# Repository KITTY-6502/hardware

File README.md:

# KITTY Computer

the KITTY is a 65c02 homebrew kit microcomputer designed around text mode graphics and cartridge media. It is fully open source, and uses exclusively in-production parts. 

Quick Specs:

* **Bus Speed:** 3Mhz
* **CPU:*** w65c02s @~2.2Mhz (average)
* **RAM:** 28Kb SRAM
* **Video:** Custom, 256x256pixels, a text mode display using a preset font, 32x32 8x8 pixel characters, 16 color palette
* **Sound:** Custom, 8x1 Wavetable Audio, 3 melodic + 1 percussive channels, all with 4bit+4bit stereo volume control.
* **Input:** 40-Key Mechanical Keyboard
* **Media/Expansion:** 2 Cartridge Slots, each with up to 128x32Kb banks.
* **Interrupts:** /IRQ triggered when the video circuit has drawn the last visible pixels on the frame.
* **Output:** RGB PAL (50hz), via a SCART connector.

**[Computer Manual](https://smaldragon.github.io/KITTY)**
**[Schematic](Docs/schematics/v2a.pdf)**

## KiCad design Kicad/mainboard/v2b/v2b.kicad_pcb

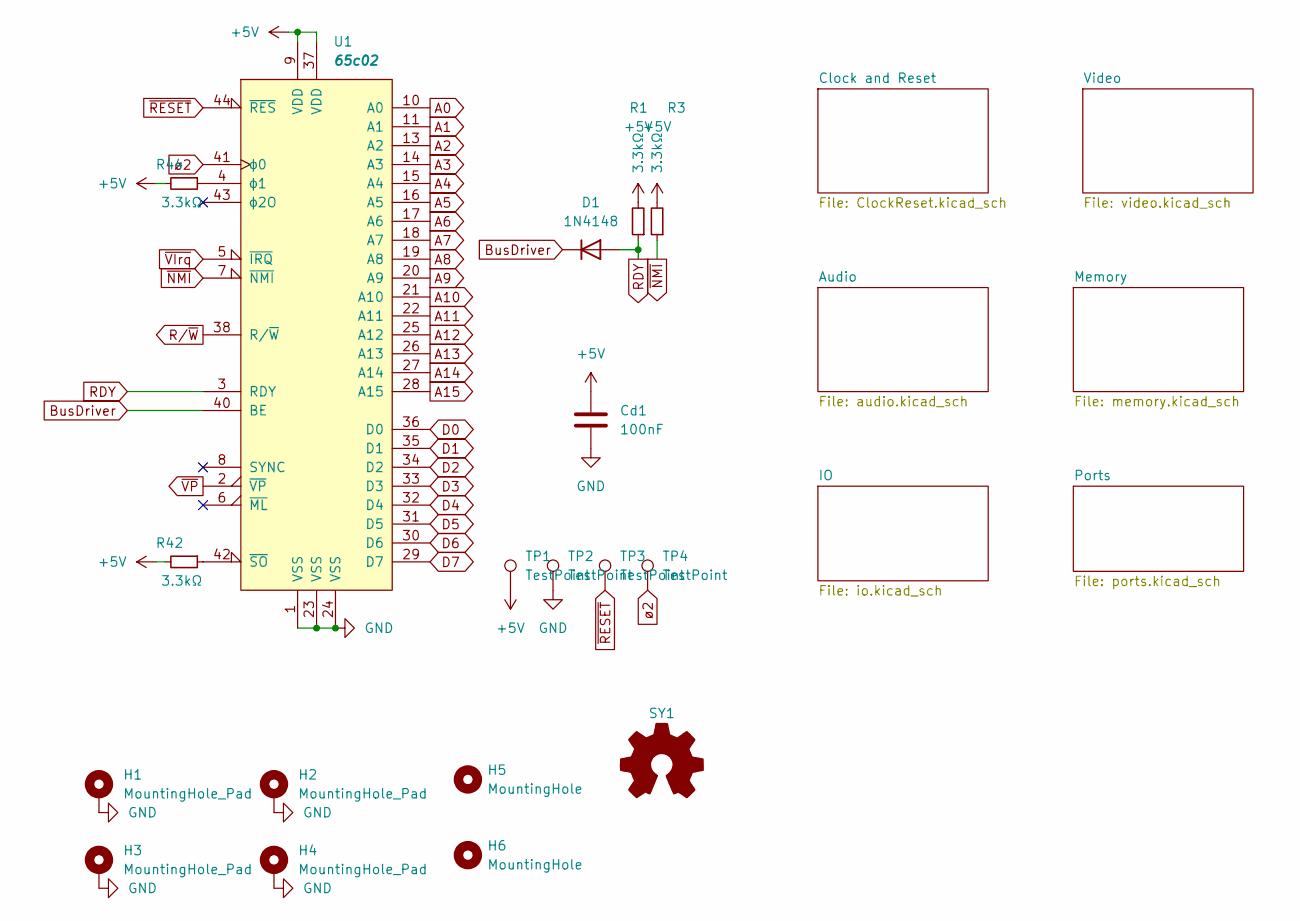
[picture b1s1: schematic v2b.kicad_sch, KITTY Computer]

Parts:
Cd1: 100nF; C_Disc_D3.0mm_W1.6mm_P2.50mm
D1: 1N4148; D_DO-34_SOD68_P7.62mm_Horizontal
H1, H2, H3, H4: MountingHole_Pad; MountingHole_3.2mm_M3_ISO14580_Pad
H5, H6: MountingHole; MountingHole_2.2mm_M2
R1, R3, R42, R44: 3.3kΩ; R_Horizontal
SY1: Logo_Open_Hardware_Small; OSHW-Logo_7.5x8mm_SilkScreen
TP1, TP2, TP3, TP4: TestPoint; TestPoint_Pad_2.0x2.0mm
U1: 65c02; PLCC-44_THT-Socket_TWEAK

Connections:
+5V: Cd1.1, R1.2, R3.2, R42.2, R44.2, TP1.1, U1.9 (VDD), U1.37 (VDD); also elsewhere on the board
A0: U1.10 (A0); also elsewhere on the board
A1: U1.11 (A1); also elsewhere on the board
A2: U1.13 (A2); also elsewhere on the board
A3: U1.14 (A3); also elsewhere on the board
A4: U1.15 (A4); also elsewhere on the board
A5: U1.16 (A5); also elsewhere on the board
A6: U1.17 (A6); also elsewhere on the board
A7: U1.18 (A7); also elsewhere on the board
A8: U1.19 (A8); also elsewhere on the board
A9: U1.20 (A9); also elsewhere on the board
A10: U1.21 (A10); also elsewhere on the board
A11: U1.22 (A11); also elsewhere on the board
A12: U1.25 (A12); also elsewhere on the board
A13: U1.26 (A13); also elsewhere on the board
A14: U1.27 (A14); also elsewhere on the board
A15: U1.28 (A15); also elsewhere on the board
BusDriver: D1.1 (K), U1.40 (BE); also elsewhere on the board
CLK2: TP4.1, U1.41 (ϕ0); also elsewhere on the board
D0: U1.36 (D0); also elsewhere on the board
D1: U1.35 (D1); also elsewhere on the board
D2: U1.34 (D2); also elsewhere on the board
D3: U1.33 (D3); also elsewhere on the board
D4: U1.32 (D4); also elsewhere on the board
D5: U1.31 (D5); also elsewhere on the board
D6: U1.30 (D6); also elsewhere on the board
D7: U1.29 (D7); also elsewhere on the board
GND: Cd1.2, H1.1, H2.1, H3.1, H4.1, TP2.1, U1.1 (VSS), U1.23 (VSS), U1.24 (VSS); also elsewhere on the board
unnamed: R42.1, U1.42 (~SO)
unnamed: R44.1, U1.4 (ϕ1)
RDY: D1.2 (A), R1.1, U1.3 (RDY)
R/~W: U1.38 (R/~W); also elsewhere on the board
~NMI: R3.1, U1.7 (~NMI); also elsewhere on the board
~RESET: TP3.1, U1.44 (~RES); also elsewhere on the board
~VIrq: U1.5 (~IRQ); also elsewhere on the board
~VP: U1.2 (~VP); also elsewhere on the board

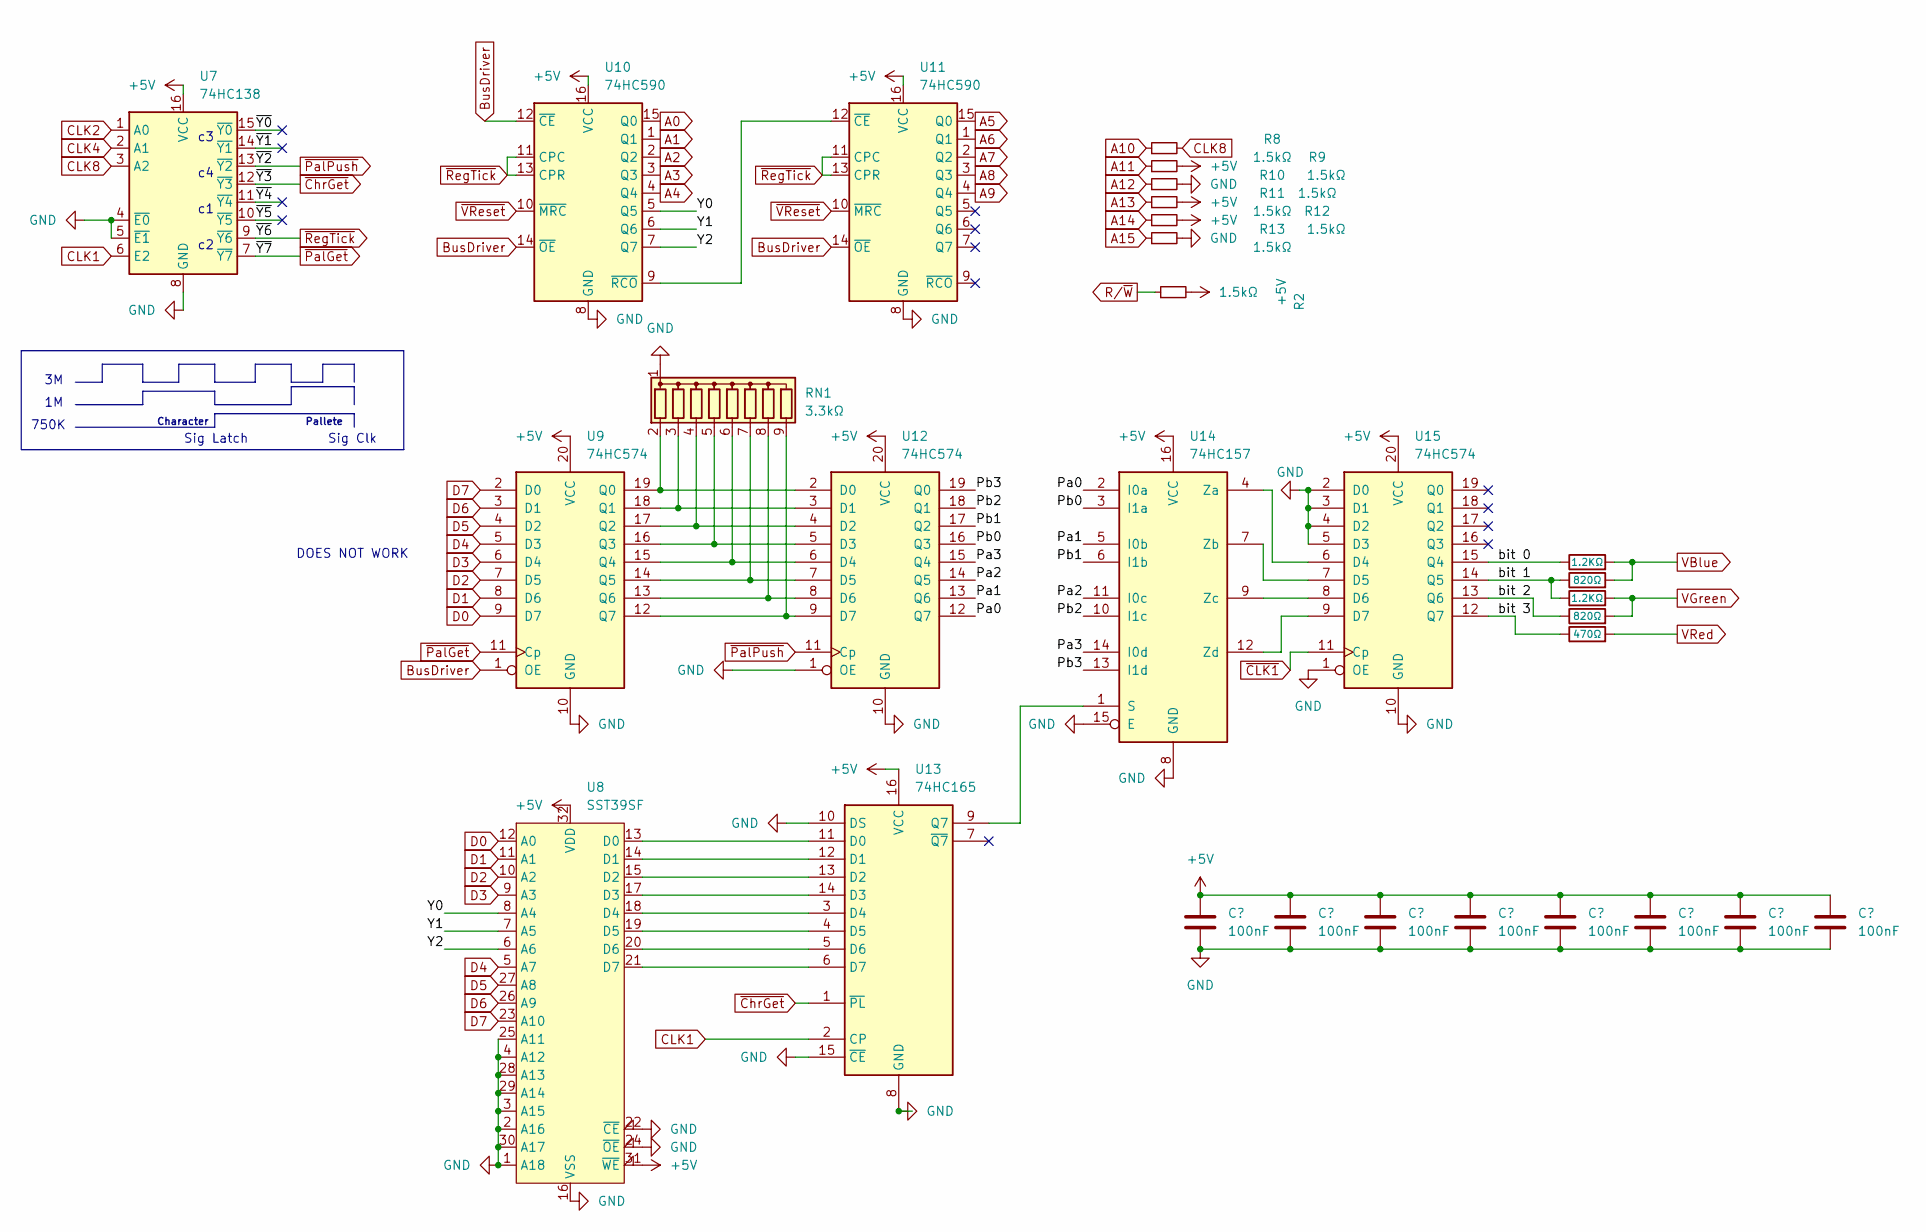
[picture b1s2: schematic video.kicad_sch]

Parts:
Cd8, Cd9, Cd10, Cd11, Cd12, Cd13, Cd14, Cd15: 100nF; C_Disc_D3.0mm_W1.6mm_P2.50mm
R2, R8, R9, R10, R11, R12, R13: 1.5kΩ; R_Horizontal
R14, R16: 1.2KΩ; R_Horizontal
R15, R17: 820Ω; R_Horizontal
R18: 470Ω; R_Horizontal
RN1: 3.3kΩ; R_Array_SIP9
U7: 74HC138; DIP-16_W7.62mm_Socket_LongPads_TWEAK
U8: SST39SF; PLCC-32_THT-Socket_TWEAK
U9, U12, U15: 74HC574; DIP-20_W7.62mm_Socket_LongPads_TWEAK
U10, U11: 74HC590; DIP-16_W7.62mm_Socket_LongPads_TWEAK
U13: 74HC165; DIP-16_W7.62mm_Socket_LongPads_TWEAK
U14: 74HC157; DIP-16_W7.62mm_Socket_LongPads_TWEAK

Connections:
+5V: Cd8.1, Cd9.1, Cd10.1, Cd11.1, Cd12.1, Cd13.1, Cd14.1, Cd15.1, R2.2, R9.2, R11.2, R12.2, U7.16 (VCC), U8.31 (~WE), U8.32 (VDD), U9.20 (VCC), U10.16 (VCC), U11.16 (VCC), U12.20 (VCC), U13.16 (VCC), U14.16 (VCC), U15.20 (VCC); also elsewhere on the board
/Video/Pa0: U12.12 (Q7), U14.2 (I0a)
/Video/Pa1: U12.13 (Q6), U14.5 (I0b)
/Video/Pa2: U12.14 (Q5), U14.11 (I0c)
/Video/Pa3: U12.15 (Q4), U14.14 (I0d)
/Video/Pb0: U12.16 (Q3), U14.3 (I1a)
/Video/Pb1: U12.17 (Q2), U14.6 (I1b)
/Video/Pb2: U12.18 (Q1), U14.10 (I1c)
/Video/Pb3: U12.19 (Q0), U14.13 (I1d)
/Video/Y0: U8.8 (A4), U10.5 (Q5)
/Video/Y1: U8.7 (A5), U10.6 (Q6)
/Video/Y2: U8.6 (A6), U10.7 (Q7)
/Video/bit 0: R14.1, U15.15 (Q4)
/Video/bit 1: R15.1, R16.1, U15.14 (Q5)
/Video/bit 2: R17.1, U15.13 (Q6)
/Video/bit 3: R18.1, U15.12 (Q7)
/Video/~Y0: U7.15 (~Y0)
/Video/~Y1: U7.14 (~Y1)
/Video/~Y4: U7.11 (~Y4)
/Video/~Y5: U7.10 (~Y5)
A0: U10.15 (Q0); also elsewhere on the board
A1: U10.1 (Q1); also elsewhere on the board
A2: U10.2 (Q2); also elsewhere on the board
A3: U10.3 (Q3); also elsewhere on the board
A4: U10.4 (Q4); also elsewhere on the board
A5: U11.15 (Q0); also elsewhere on the board
A6: U11.1 (Q1); also elsewhere on the board
A7: U11.2 (Q2); also elsewhere on the board
A8: U11.3 (Q3); also elsewhere on the board
A9: U11.4 (Q4); also elsewhere on the board
A10: R8.1; also elsewhere on the board
A11: R9.1; also elsewhere on the board
A12: R10.1; also elsewhere on the board
A13: R11.1; also elsewhere on the board
A14: R12.1; also elsewhere on the board
A15: R13.1; also elsewhere on the board
BusDriver: U9.1 (OE), U10.12 (~CE), U10.14 (~OE), U11.14 (~OE); also elsewhere on the board
CLK1: U7.6 (E2), U13.2 (CP); also elsewhere on the board
CLK2: U7.1 (A0); also elsewhere on the board
CLK4: U7.2 (A1); also elsewhere on the board
CLK8: R8.2, U7.3 (A2); also elsewhere on the board
D0: U8.12 (A0), U9.9 (D7); also elsewhere on the board
D1: U8.11 (A1), U9.8 (D6); also elsewhere on the board
D2: U8.10 (A2), U9.7 (D5); also elsewhere on the board
D3: U8.9 (A3), U9.6 (D4); also elsewhere on the board
D4: U8.5 (A7), U9.5 (D3); also elsewhere on the board
D5: U8.27 (A8), U9.4 (D2); also elsewhere on the board
D6: U8.26 (A9), U9.3 (D1); also elsewhere on the board
D7: U8.23 (A10), U9.2 (D0); also elsewhere on the board
GND: Cd8.2, Cd9.2, Cd10.2, Cd11.2, Cd12.2, Cd13.2, Cd14.2, Cd15.2, R10.2, R13.2, RN1.1 (common), U7.4 (~E0), U7.5 (~E1), U7.8 (GND), U8.1 (A18), U8.2 (A16), U8.3 (A15), U8.4 (A12), U8.16 (VSS), U8.22 (~CE), U8.24 (~OE), U8.25 (A11), U8.28 (A13), U8.29 (A14), U8.30 (A17), U9.10 (GND), U10.8 (GND), U11.8 (GND), U12.1 (OE), U12.10 (GND), U13.8 (GND), U13.10 (DS), U13.15 (~CE), U14.8 (GND), U14.15 (E), U15.1 (OE), U15.2 (D0), U15.3 (D1), U15.4 (D2), U15.5 (D3), U15.10 (GND); also elsewhere on the board
unnamed: RN1.2 (R1), U9.19 (Q0), U12.2 (D0)
unnamed: RN1.3 (R2), U9.18 (Q1), U12.3 (D1)
unnamed: RN1.4 (R3), U9.17 (Q2), U12.4 (D2)
unnamed: RN1.5 (R4), U9.16 (Q3), U12.5 (D3)
unnamed: RN1.6 (R5), U9.15 (Q4), U12.6 (D4)
unnamed: RN1.7 (R6), U9.14 (Q5), U12.7 (D5)
unnamed: RN1.8 (R7), U9.13 (Q6), U12.8 (D6)
unnamed: RN1.9 (R8), U9.12 (Q7), U12.9 (D7)
unnamed: U10.9 (~RCO), U11.12 (~CE)
unnamed: U8.13 (D0), U13.11 (D0)
unnamed: U8.14 (D1), U13.12 (D1)
unnamed: U8.15 (D2), U13.13 (D2)
unnamed: U8.17 (D3), U13.14 (D3)
unnamed: U8.18 (D4), U13.3 (D4)
unnamed: U8.19 (D5), U13.4 (D5)
unnamed: U8.20 (D6), U13.5 (D6)
unnamed: U8.21 (D7), U13.6 (D7)
unnamed: U13.9 (Q7), U14.1 (S)
unnamed: U14.4 (Za), U15.6 (D4)
unnamed: U14.7 (Zb), U15.7 (D5)
unnamed: U14.9 (Zc), U15.8 (D6)
unnamed: U14.12 (Zd), U15.9 (D7)
R/~W: R2.1; also elsewhere on the board
VBlue: R14.2, R15.2; also elsewhere on the board
VGreen: R16.2, R17.2; also elsewhere on the board
VRed: R18.2; also elsewhere on the board
~CLK1: U15.11 (Cp); also elsewhere on the board
~ChrGet: U7.12 (~Y3), U13.1 (~PL)
~PalGet: U7.7 (~Y7), U9.11 (Cp)
~PalPush: U7.13 (~Y2), U12.11 (Cp)
~RegTick: U7.9 (~Y6), U10.11 (CPC), U10.13 (CPR), U11.11 (CPC), U11.13 (CPR)
~VReset: U10.10 (~MRC), U11.10 (~MRC); also elsewhere on the board

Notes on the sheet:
Pallete
750K
Sig Clk
Character
DOES NOT WORK
Sig Latch

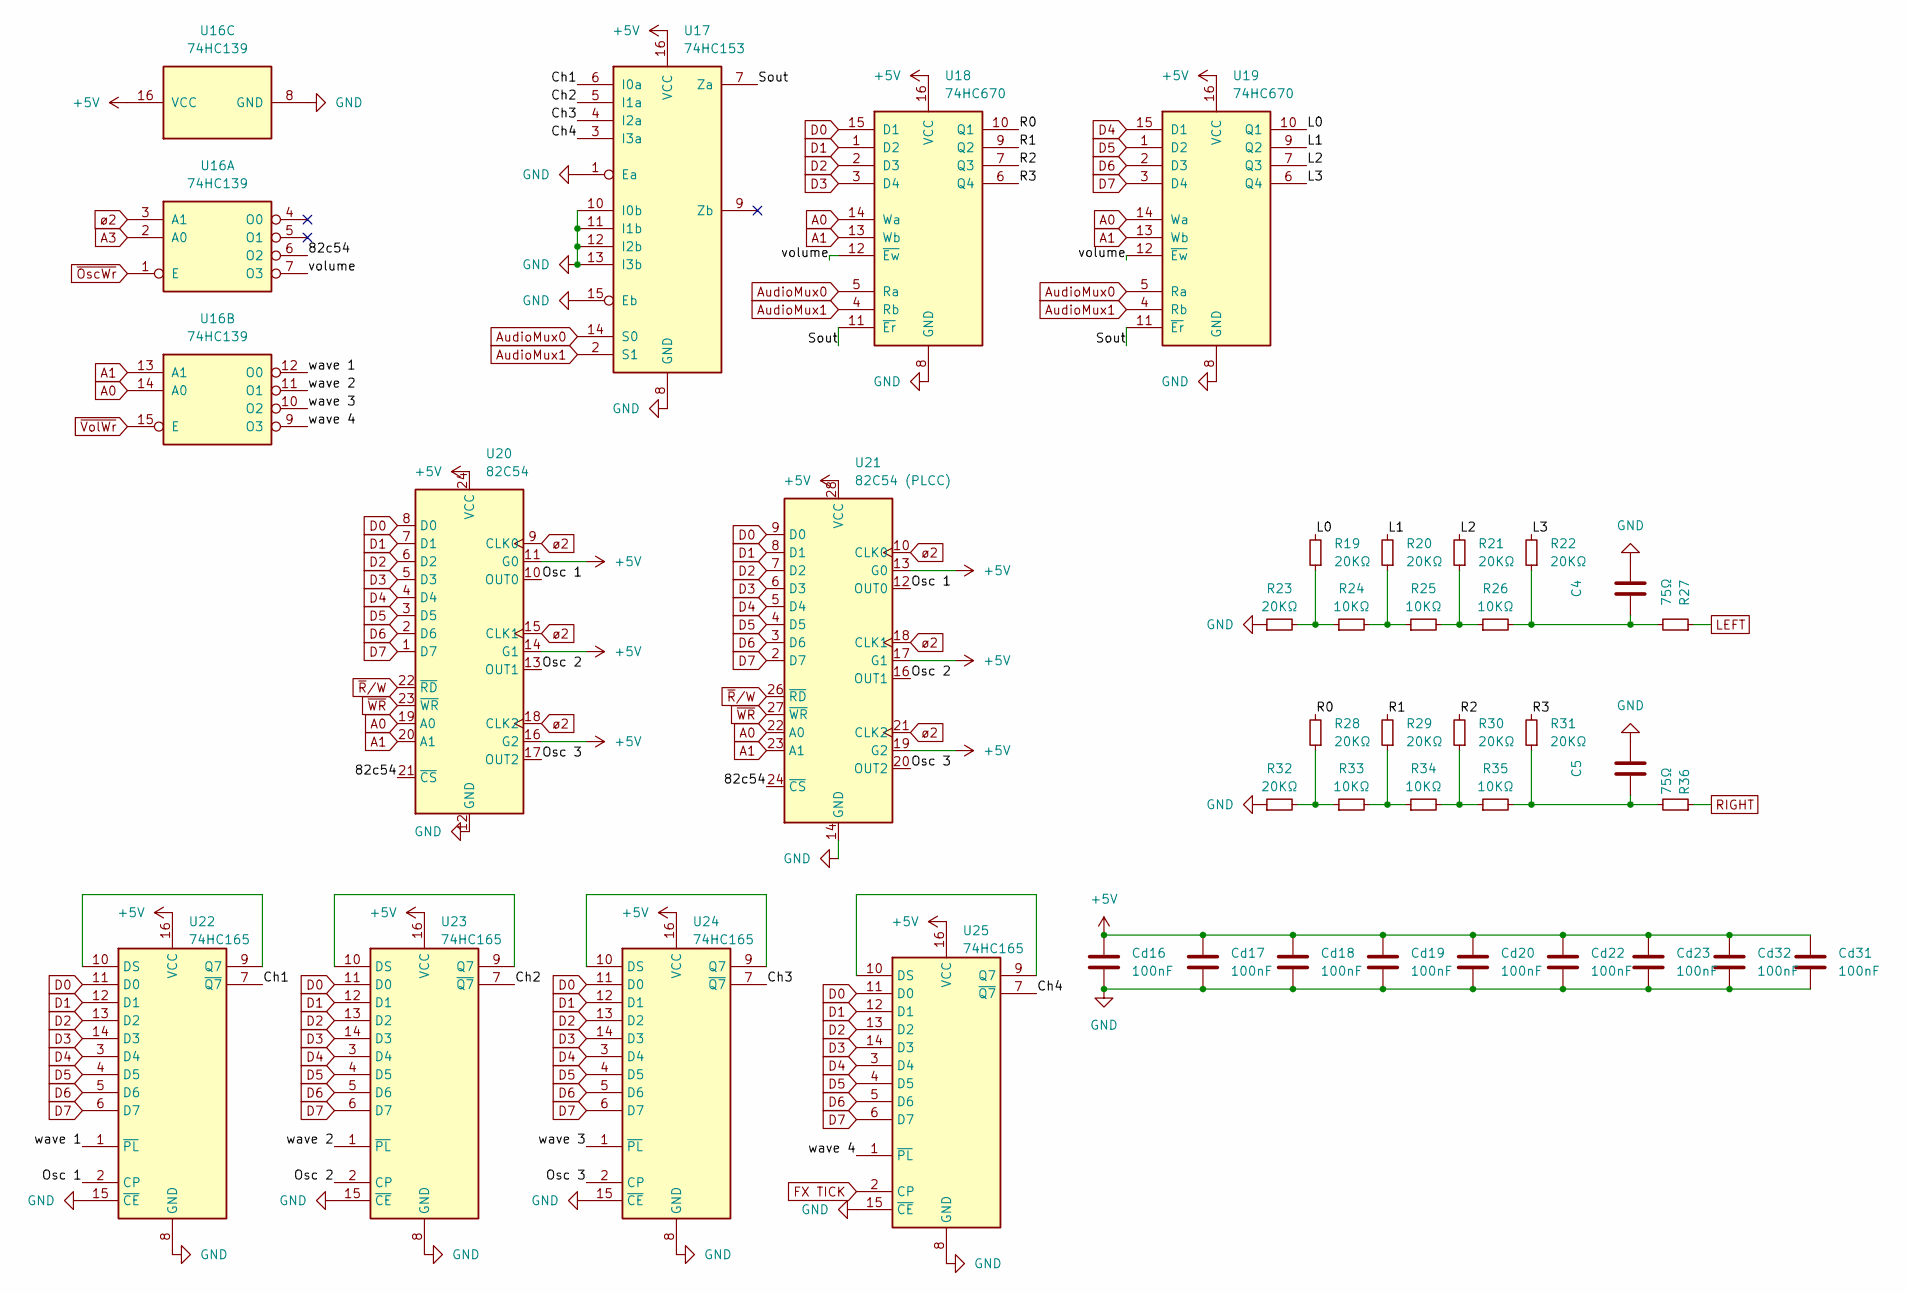
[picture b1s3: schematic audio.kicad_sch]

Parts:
C4, C5: 100nF; C_Disc_D3.0mm_W1.6mm_P2.50mm
Cd16, Cd17, Cd18, Cd19, Cd20, Cd22, Cd23, Cd31, Cd32: 100nF; C_Disc_D3.0mm_W1.6mm_P2.50mm
R19, R20, R21, R22, R23, R28, R29, R30, R31, R32: 20KΩ; RESISTOR VERT_WIDE
R24, R25, R26, R33, R34, R35: 10KΩ; RESISTOR VERT_WIDE
R27, R36: 75Ω; RESISTOR VERT_WIDE
U16: 74HC139; DIP-16_W7.62mm_Socket_LongPads_TWEAK
U17: 74HC153; DIP-16_W7.62mm_Socket_LongPads_TWEAK
U18, U19: 74HC670; DIP-16_W7.62mm_Socket_LongPads_TWEAK
U20: 82C54; DIP-24_W15.24mm_Socket_TWEAK
U21: 82C54 (PLCC); PLCC-28_THT-Socket_TWEAK
U22, U23, U24, U25: 74HC165; DIP-16_W7.62mm_Socket_LongPads_TWEAK

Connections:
+5V: Cd16.1, Cd17.1, Cd18.1, Cd19.1, Cd20.1, Cd22.1, Cd23.1, Cd31.1, Cd32.1, U16.16 (VCC), U17.16 (VCC), U18.16 (VCC), U19.16 (VCC), U20.11 (G0), U20.14 (G1), U20.16 (G2), U20.24 (VCC), U21.13 (G0), U21.17 (G1), U21.19 (G2), U21.28 (VCC), U22.16 (VCC), U23.16 (VCC), U24.16 (VCC), U25.16 (VCC); also elsewhere on the board
/Audio/82c54: U16.6 (O2), U20.21 (~CS), U21.24 (~CS)
/Audio/Ch1: U17.6 (I0a), U22.7 (~Q7)
/Audio/Ch2: U17.5 (I1a), U23.7 (~Q7)
/Audio/Ch3: U17.4 (I2a), U24.7 (~Q7)
/Audio/Ch4: U17.3 (I3a), U25.7 (~Q7)
/Audio/L0: R19.2, U19.10 (Q1)
/Audio/L1: R20.2, U19.9 (Q2)
/Audio/L2: R21.2, U19.7 (Q3)
/Audio/L3: R22.2, U19.6 (Q4)
/Audio/Osc 1: U20.10 (OUT0), U21.12 (OUT0), U22.2 (CP)
/Audio/Osc 2: U20.13 (OUT1), U21.16 (OUT1), U23.2 (CP)
/Audio/Osc 3: U20.17 (OUT2), U21.20 (OUT2), U24.2 (CP)
/Audio/R0: R28.2, U18.10 (Q1)
/Audio/R1: R29.2, U18.9 (Q2)
/Audio/R2: R30.2, U18.7 (Q3)
/Audio/R3: R31.2, U18.6 (Q4)
/Audio/Sout: U17.7 (Za), U18.11 (~Er), U19.11 (~Er)
/Audio/volume: U16.7 (O3), U18.12 (~Ew), U19.12 (~Ew)
/Audio/wave 1: U16.12 (O0), U22.1 (~PL)
/Audio/wave 2: U16.11 (O1), U23.1 (~PL)
/Audio/wave 3: U16.10 (O2), U24.1 (~PL)
/Audio/wave 4: U16.9 (O3), U25.1 (~PL)
A0: U16.14 (A0), U18.14 (Wa), U19.14 (Wa), U20.19 (A0), U21.22 (A0); also elsewhere on the board
A1: U16.13 (A1), U18.13 (Wb), U19.13 (Wb), U20.20 (A1), U21.23 (A1); also elsewhere on the board
A3: U16.2 (A0); also elsewhere on the board
AudioMux0: U17.14 (S0), U18.5 (Ra), U19.5 (Ra); also elsewhere on the board
AudioMux1: U17.2 (S1), U18.4 (Rb), U19.4 (Rb); also elsewhere on the board
CLK2: U16.3 (A1), U20.9 (CLK0), U20.15 (CLK1), U20.18 (CLK2), U21.10 (CLK0), U21.18 (CLK1), U21.21 (CLK2); also elsewhere on the board
D0: U18.15 (D1), U20.8 (D0), U21.9 (D0), U22.11 (D0), U23.11 (D0), U24.11 (D0), U25.11 (D0); also elsewhere on the board
D1: U18.1 (D2), U20.7 (D1), U21.8 (D1), U22.12 (D1), U23.12 (D1), U24.12 (D1), U25.12 (D1); also elsewhere on the board
D2: U18.2 (D3), U20.6 (D2), U21.7 (D2), U22.13 (D2), U23.13 (D2), U24.13 (D2), U25.13 (D2); also elsewhere on the board
D3: U18.3 (D4), U20.5 (D3), U21.6 (D3), U22.14 (D3), U23.14 (D3), U24.14 (D3), U25.14 (D3); also elsewhere on the board
D4: U19.15 (D1), U20.4 (D4), U21.5 (D4), U22.3 (D4), U23.3 (D4), U24.3 (D4), U25.3 (D4); also elsewhere on the board
D5: U19.1 (D2), U20.3 (D5), U21.4 (D5), U22.4 (D5), U23.4 (D5), U24.4 (D5), U25.4 (D5); also elsewhere on the board
D6: U19.2 (D3), U20.2 (D6), U21.3 (D6), U22.5 (D6), U23.5 (D6), U24.5 (D6), U25.5 (D6); also elsewhere on the board
D7: U19.3 (D4), U20.1 (D7), U21.2 (D7), U22.6 (D7), U23.6 (D7), U24.6 (D7), U25.6 (D7); also elsewhere on the board
FX TICK: U25.2 (CP); also elsewhere on the board
GND: C4.1, C5.1, Cd16.2, Cd17.2, Cd18.2, Cd19.2, Cd20.2, Cd22.2, Cd23.2, Cd31.2, Cd32.2, R23.1, R32.1, U16.8 (GND), U17.1 (Ea), U17.8 (GND), U17.10 (I0b), U17.11 (I1b), U17.12 (I2b), U17.13 (I3b), U17.15 (Eb), U18.8 (GND), U19.8 (GND), U20.12 (GND), U21.14 (GND), U22.8 (GND), U22.15 (~CE), U23.8 (GND), U23.15 (~CE), U24.8 (GND), U24.15 (~CE), U25.8 (GND), U25.15 (~CE); also elsewhere on the board
LEFT: R27.1; also elsewhere on the board
unnamed: C4.2, R22.1, R26.2, R27.2
unnamed: C5.2, R31.1, R35.2, R36.2
unnamed: R19.1, R23.2, R24.1
unnamed: R20.1, R24.2, R25.1
unnamed: R21.1, R25.2, R26.1
unnamed: R28.1, R32.2, R33.1
unnamed: R29.1, R33.2, R34.1
unnamed: R30.1, R34.2, R35.1
unnamed: U22.9 (Q7), U22.10 (DS)
unnamed: U23.9 (Q7), U23.10 (DS)
unnamed: U24.9 (Q7), U24.10 (DS)
unnamed: U25.9 (Q7), U25.10 (DS)
RIGHT: R36.1; also elsewhere on the board
~OscWr: U16.1 (E); also elsewhere on the board
~R/W: U20.22 (~RD), U21.26 (~RD); also elsewhere on the board
~VolWr: U16.15 (E); also elsewhere on the board
~WR: U20.23 (~WR), U21.27 (~WR); also elsewhere on the board

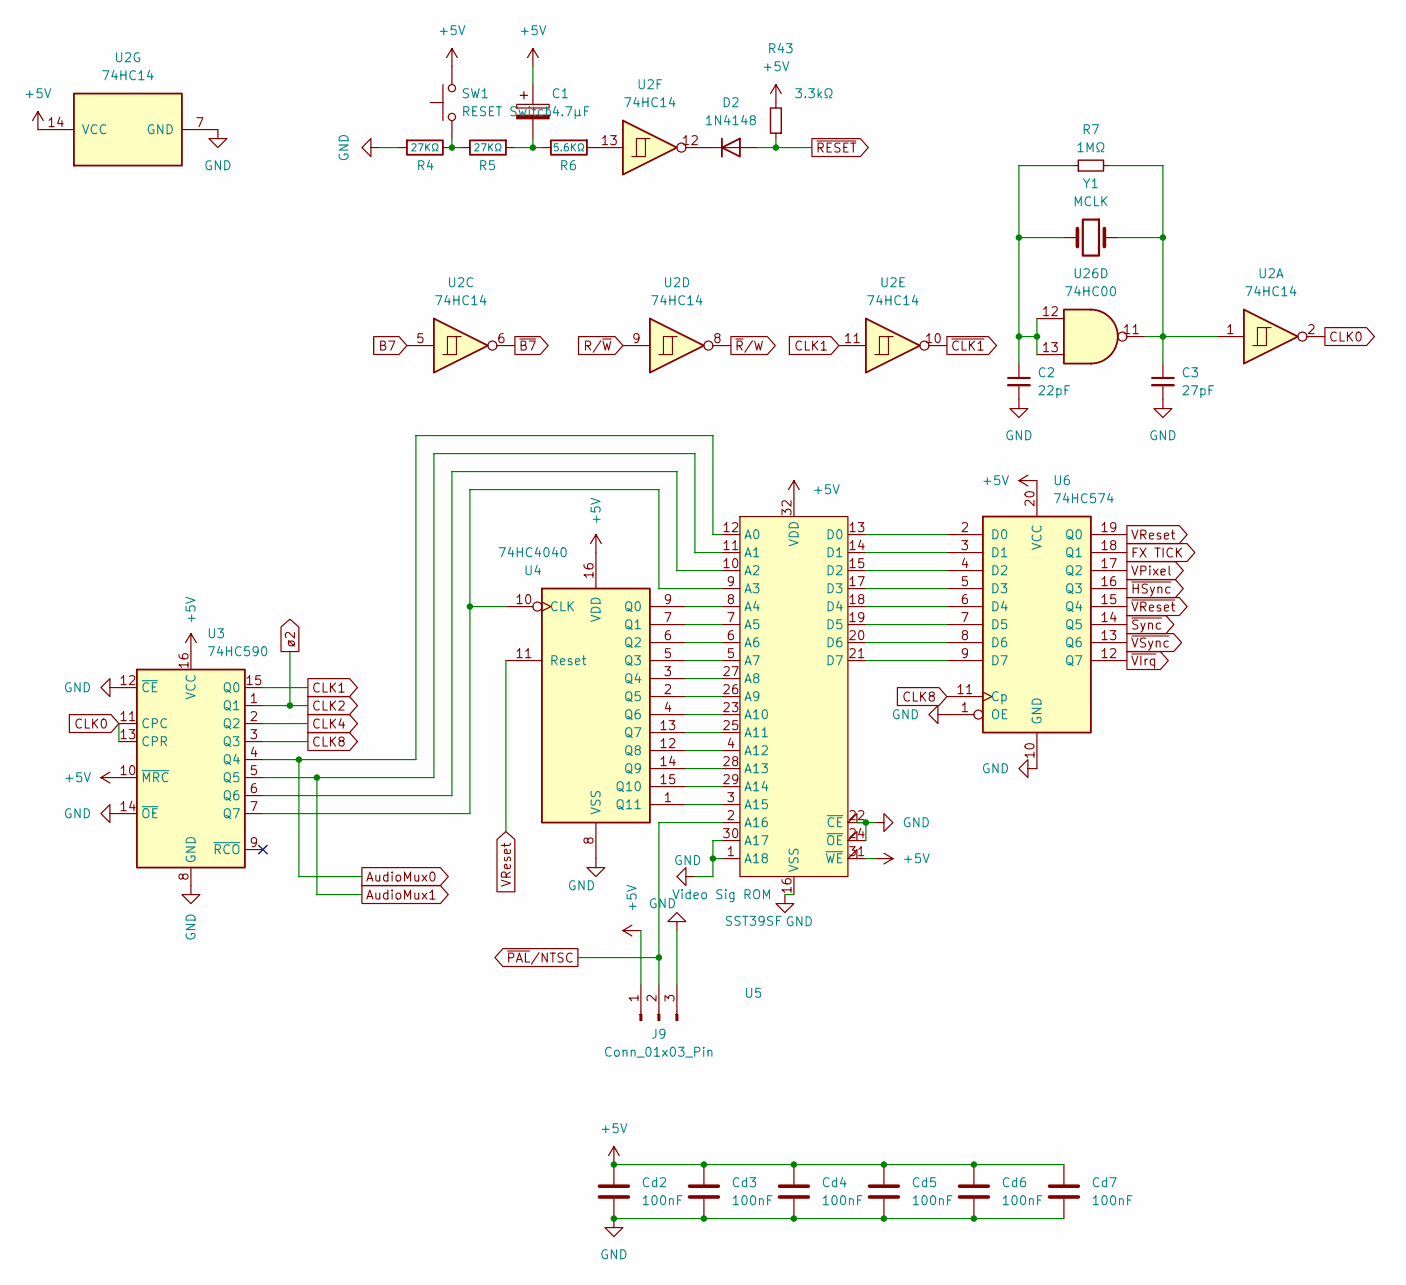
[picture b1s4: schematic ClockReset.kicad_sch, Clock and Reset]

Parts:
C1: 4.7µF; CP_Radial_D4.0mm_P1.50mm
C2: 22pF; C_Disc_D3.0mm_W1.6mm_P2.50mm
C3: 27pF; C_Disc_D3.0mm_W1.6mm_P2.50mm
Cd2, Cd3, Cd4, Cd5, Cd6, Cd7: 100nF; C_Disc_D3.0mm_W1.6mm_P2.50mm
D2: 1N4148; D_DO-34_SOD68_P7.62mm_Horizontal
J9: Conn_01x03_Pin; PinHeader_1x03_P2.54mm_Vertical
R4, R5: 27KΩ; R_Horizontal
R6: 5.6KΩ; R_Horizontal
R7: 1MΩ; R_Horizontal
R43: 3.3kΩ; R_Horizontal
SW1: RESET Switch; SW_Tactile_SPST_Angled_PTS645Vx83-2LFS
U2: 74HC14; DIP-14_W7.62mm_Socket_LongPads_TWEAK
U3: 74HC590; DIP-16_W7.62mm_Socket_LongPads_TWEAK
U4: 74HC4040; DIP-16_W7.62mm_Socket_LongPads_TWEAK
U5: SST39SF; PLCC-32_THT-Socket_TWEAK
U6: 74HC574; DIP-20_W7.62mm_Socket_LongPads_TWEAK
U26: 74HC00; DIP-14_W7.62mm_Socket_LongPads_TWEAK
Y1: MCLK; Crystal_HC49-U_Vertical

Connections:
+5V: C1.1, Cd2.1, Cd3.1, Cd4.1, Cd5.1, Cd6.1, Cd7.1, J9.1, R43.2, SW1.2, U2.14 (VCC), U3.10 (~MRC), U3.16 (VCC), U4.16 (VDD), U5.31 (~WE), U5.32 (VDD), U6.20 (VCC); also elsewhere on the board
AudioMux0: U3.4 (Q4), U5.12 (A0); also elsewhere on the board
AudioMux1: U3.5 (Q5), U5.11 (A1); also elsewhere on the board
B7: U2.5; also elsewhere on the board
CLK0: U2.2, U3.11 (CPC), U3.13 (CPR)
CLK1: U2.11, U3.15 (Q0); also elsewhere on the board
CLK2: U3.1 (Q1); also elsewhere on the board
CLK4: U3.2 (Q2); also elsewhere on the board
CLK8: U3.3 (Q3), U6.11 (Cp); also elsewhere on the board
FX TICK: U6.18 (Q1); also elsewhere on the board
GND: C2.2, C3.2, Cd2.2, Cd3.2, Cd4.2, Cd5.2, Cd6.2, Cd7.2, J9.3, R4.2, U2.7 (GND), U3.8 (GND), U3.12 (~CE), U3.14 (~OE), U4.8 (VSS), U5.1 (A18), U5.16 (VSS), U5.22 (~CE), U5.24 (~OE), U5.30 (A17), U6.1 (OE), U6.10 (GND); also elsewhere on the board
unnamed: C1.2, R5.2, R6.1
unnamed: C2.1, R7.1, U26.12, U26.13, Y1.2
unnamed: C3.1, R7.2, U2.1, U26.11, Y1.1
unnamed: D2.1 (K), U2.12
unnamed: R4.1, R5.1, SW1.1
unnamed: R6.2, U2.13
unnamed: U3.6 (Q6), U5.10 (A2)
unnamed: U3.7 (Q7), U4.10 (CLK), U5.9 (A3)
unnamed: U4.9 (Q0), U5.8 (A4)
unnamed: U4.7 (Q1), U5.7 (A5)
unnamed: U4.6 (Q2), U5.6 (A6)
unnamed: U4.5 (Q3), U5.5 (A7)
unnamed: U4.3 (Q4), U5.27 (A8)
unnamed: U4.2 (Q5), U5.26 (A9)
unnamed: U4.4 (Q6), U5.23 (A10)
unnamed: U4.13 (Q7), U5.25 (A11)
unnamed: U4.12 (Q8), U5.4 (A12)
unnamed: U4.14 (Q9), U5.28 (A13)
unnamed: U4.15 (Q10), U5.29 (A14)
unnamed: U4.1 (Q11), U5.3 (A15)
unnamed: U5.13 (D0), U6.2 (D0)
unnamed: U5.14 (D1), U6.3 (D1)
unnamed: U5.15 (D2), U6.4 (D2)
unnamed: U5.17 (D3), U6.5 (D3)
unnamed: U5.18 (D4), U6.6 (D4)
unnamed: U5.19 (D5), U6.7 (D5)
unnamed: U5.20 (D6), U6.8 (D6)
unnamed: U5.21 (D7), U6.9 (D7)
R/~W: U2.9; also elsewhere on the board
VPixel: U6.17 (Q2); also elsewhere on the board
VReset: U4.11 (Reset), U6.19 (Q0)
~B7: U2.6; also elsewhere on the board
~CLK1: U2.10; also elsewhere on the board
~HSync: U6.16 (Q3); also elsewhere on the board
~PAL/NTSC: J9.2, U5.2 (A16)
~RESET: D2.2 (A), R43.1; also elsewhere on the board
~R/W: U2.8; also elsewhere on the board
~Sync: U6.14 (Q5); also elsewhere on the board
~VIrq: U6.12 (Q7); also elsewhere on the board
~VReset: U6.15 (Q4); also elsewhere on the board
~VSync: U6.13 (Q6); also elsewhere on the board

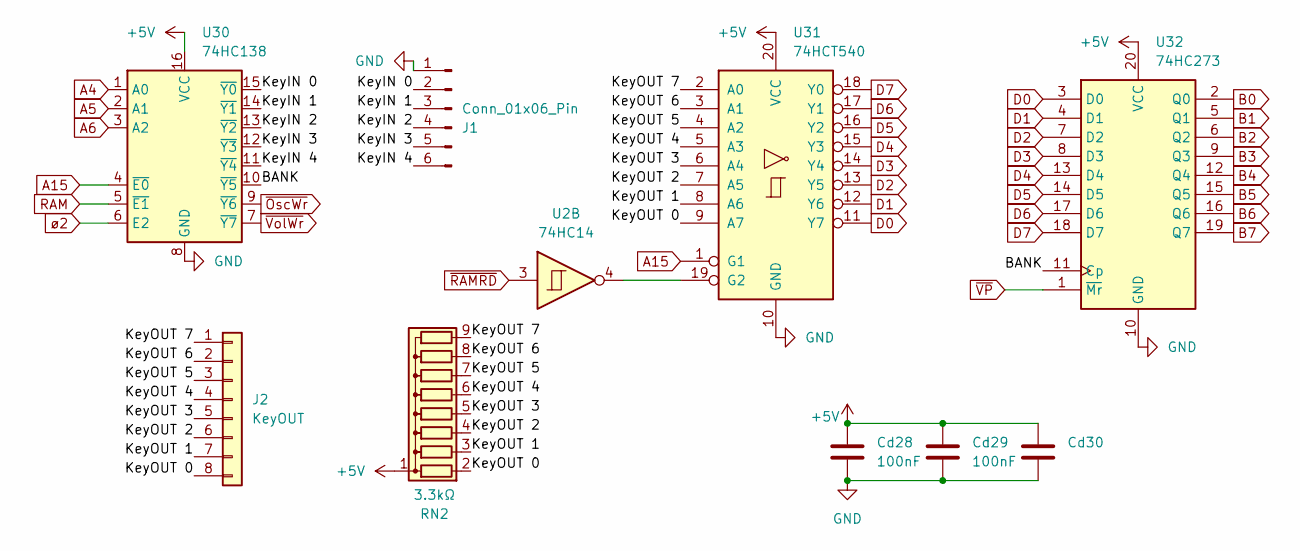
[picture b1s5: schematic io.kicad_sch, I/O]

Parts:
Cd28, Cd29, Cd30: 100nF; C_Disc_D3.0mm_W1.6mm_P2.50mm
J1: Conn_01x06_Pin; PinHeader_1x06_P2.54mm_Vertical
J2: KeyOUT; PinHeader_1x08_P2.54mm_Vertical
RN2: 3.3kΩ; R_Array_SIP9
U2: 74HC14; DIP-14_W7.62mm_Socket_LongPads_TWEAK
U30: 74HC138; DIP-16_W7.62mm_Socket_LongPads_TWEAK
U31: 74HCT540; DIP-20_W7.62mm_Socket_LongPads_TWEAK
U32: 74HC273; DIP-20_W7.62mm_Socket_LongPads_TWEAK

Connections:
+5V: Cd28.1, Cd29.1, Cd30.1, RN2.1 (common), U30.16 (VCC), U31.20 (VCC), U32.20 (VCC); also elsewhere on the board
/IO/BANK: U30.10 (~Y5), U32.11 (Cp)
/IO/KeyIN 0: J1.2, U30.15 (~Y0)
/IO/KeyIN 1: J1.3, U30.14 (~Y1)
/IO/KeyIN 2: J1.4, U30.13 (~Y2)
/IO/KeyIN 3: J1.5, U30.12 (~Y3)
/IO/KeyIN 4: J1.6, U30.11 (~Y4)
/IO/KeyOUT 0: J2.8, RN2.2 (R1), U31.9 (A7)
/IO/KeyOUT 1: J2.7, RN2.3 (R2), U31.8 (A6)
/IO/KeyOUT 2: J2.6, RN2.4 (R3), U31.7 (A5)
/IO/KeyOUT 3: J2.5, RN2.5 (R4), U31.6 (A4)
/IO/KeyOUT 4: J2.4, RN2.6 (R5), U31.5 (A3)
/IO/KeyOUT 5: J2.3, RN2.7 (R6), U31.4 (A2)
/IO/KeyOUT 6: J2.2, RN2.8 (R7), U31.3 (A1)
/IO/KeyOUT 7: J2.1, RN2.9 (R8), U31.2 (A0)
A4: U30.1 (A0); also elsewhere on the board
A5: U30.2 (A1); also elsewhere on the board
A6: U30.3 (A2); also elsewhere on the board
A15: U30.4 (~E0), U31.1 (G1); also elsewhere on the board
B0: U32.2 (Q0); also elsewhere on the board
B1: U32.5 (Q1); also elsewhere on the board
B2: U32.6 (Q2); also elsewhere on the board
B3: U32.9 (Q3); also elsewhere on the board
B4: U32.12 (Q4); also elsewhere on the board
B5: U32.15 (Q5); also elsewhere on the board
B6: U32.16 (Q6); also elsewhere on the board
B7: U32.19 (Q7); also elsewhere on the board
CLK2: U30.6 (E2); also elsewhere on the board
D0: U31.11 (Y7), U32.3 (D0); also elsewhere on the board
D1: U31.12 (Y6), U32.4 (D1); also elsewhere on the board
D2: U31.13 (Y5), U32.7 (D2); also elsewhere on the board
D3: U31.14 (Y4), U32.8 (D3); also elsewhere on the board
D4: U31.15 (Y3), U32.13 (D4); also elsewhere on the board
D5: U31.16 (Y2), U32.14 (D5); also elsewhere on the board
D6: U31.17 (Y1), U32.17 (D6); also elsewhere on the board
D7: U31.18 (Y0), U32.18 (D7); also elsewhere on the board
GND: Cd28.2, Cd29.2, Cd30.2, J1.1, U30.8 (GND), U31.10 (GND), U32.10 (GND); also elsewhere on the board
unnamed: U2.4, U31.19 (G2)
RAM: U30.5 (~E1); also elsewhere on the board
~OscWr: U30.9 (~Y6); also elsewhere on the board
~RAMRD: U2.3; also elsewhere on the board
~VP: U32.1 (~Mr); also elsewhere on the board
~VolWr: U30.7 (~Y7); also elsewhere on the board

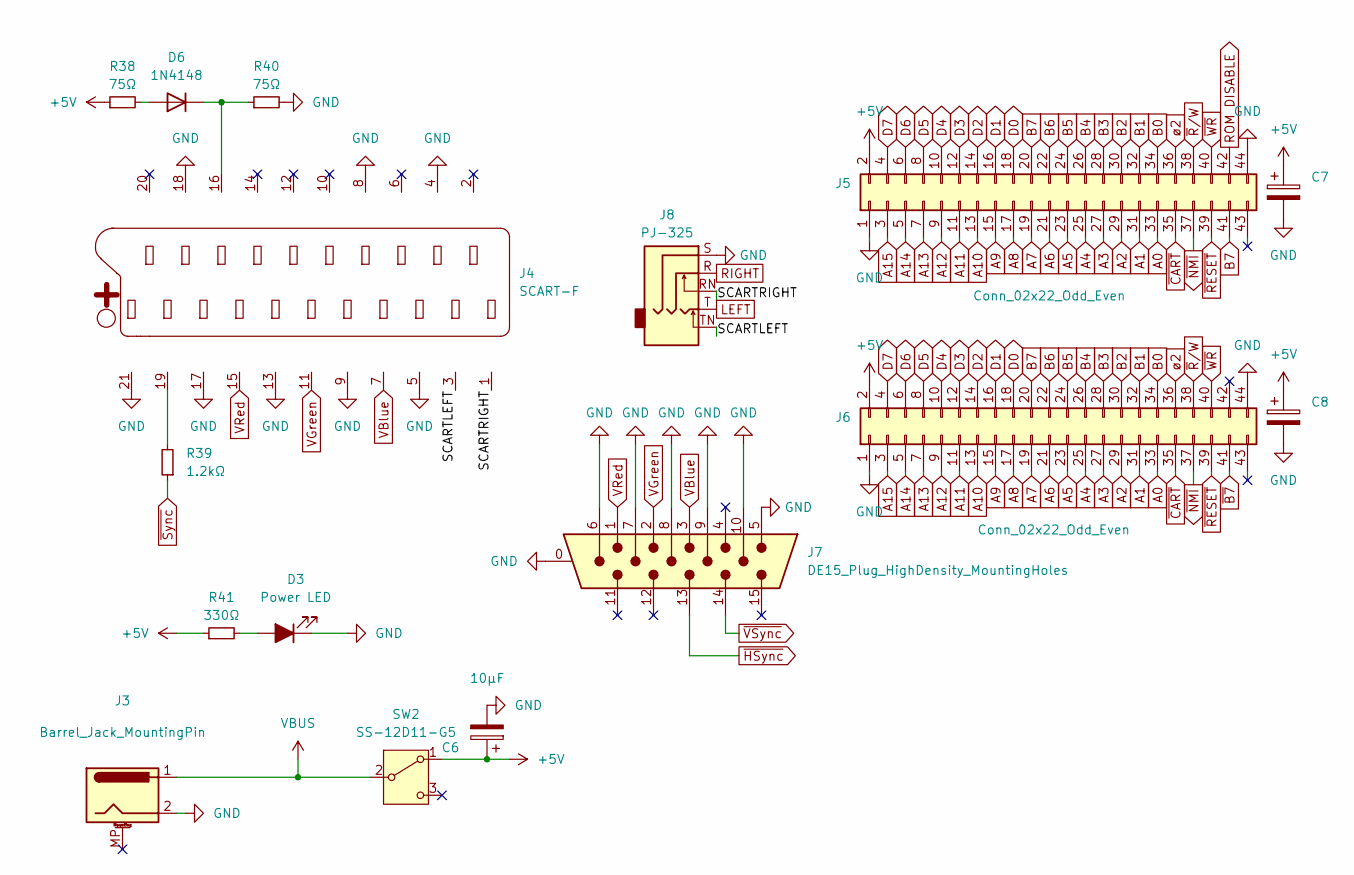
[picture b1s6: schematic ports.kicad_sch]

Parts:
C6, C7, C8: 10µF; CP_Radial_D6.3mm_P3.8mm
D3: Power LED; LED_Rectangular_W5.0mm_H2.0mm
D6: 1N4148; D_DO-34_SOD68_P7.62mm_Horizontal
J3: Barrel_Jack_MountingPin; BarrelJack_Horizontal
J4: SCART-F; SCART
J5, J6: Conn_02x22_Odd_Even; EdgeHeader_2x22_P2.54mm_Vertical
J7: DE15_Plug_HighDensity_MountingHoles; DSUB-15-HD_Female_Horizontal_P2.29x1.98mm_EdgePinOffset8.35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
J8: PJ-325; Jack_3.5mm_PJ-325
R38, R40: 75Ω; R_Horizontal
R39: 1.2kΩ; R_Horizontal
R41: 330Ω; R_Horizontal
SW2: SS-12D11-G5; SW_Slide_1P2T_CK_OS102011MS2Q

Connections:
+5V: C6.1, C7.1, C8.1, J5.2, J6.2, R38.1, R41.1, SW2.1 (A); also elsewhere on the board
/Ports/SCARTLEFT: J4.3, J8.TN
/Ports/SCARTRIGHT: J4.1, J8.RN
A0: J5.33, J6.33; also elsewhere on the board
A1: J5.31, J6.31; also elsewhere on the board
A2: J5.29, J6.29; also elsewhere on the board
A3: J5.27, J6.27; also elsewhere on the board
A4: J5.25, J6.25; also elsewhere on the board
A5: J5.23, J6.23; also elsewhere on the board
A6: J5.21, J6.21; also elsewhere on the board
A7: J5.19, J6.19; also elsewhere on the board
A8: J5.17, J6.17; also elsewhere on the board
A9: J5.15, J6.15; also elsewhere on the board
A10: J5.13, J6.13; also elsewhere on the board
A11: J5.11, J6.11; also elsewhere on the board
A12: J5.9, J6.9; also elsewhere on the board
A13: J5.7, J6.7; also elsewhere on the board
A14: J5.5, J6.5; also elsewhere on the board
A15: J5.3, J6.3; also elsewhere on the board
B0: J5.34, J6.34; also elsewhere on the board
B1: J5.32, J6.32; also elsewhere on the board
B2: J5.30, J6.30; also elsewhere on the board
B3: J5.28, J6.28; also elsewhere on the board
B4: J5.26, J6.26; also elsewhere on the board
B5: J5.24, J6.24; also elsewhere on the board
B6: J5.22, J6.22; also elsewhere on the board
B7: J5.20, J5.41, J6.20; also elsewhere on the board
CLK2: J5.36, J6.36; also elsewhere on the board
D0: J5.18, J6.18; also elsewhere on the board
D1: J5.16, J6.16; also elsewhere on the board
D2: J5.14, J6.14; also elsewhere on the board
D3: J5.12, J6.12; also elsewhere on the board
D4: J5.10, J6.10; also elsewhere on the board
D5: J5.8, J6.8; also elsewhere on the board
D6: J5.6, J6.6; also elsewhere on the board
D7: J5.4, J6.4; also elsewhere on the board
GND: C6.2, C7.2, C8.2, D3.1 (K), J3.2, J4.4, J4.5, J4.8, J4.9, J4.13, J4.17, J4.18, J4.21, J5.1, J5.44, J6.1, J6.44, J7.0, J7.5, J7.6, J7.7, J7.8, J7.9, J7.10, J8.S, R40.2; also elsewhere on the board
LEFT: J8.T; also elsewhere on the board
unnamed: D3.2 (A), R41.2
unnamed: D6.2 (A), R38.2
unnamed: D6.1 (K), J4.16, R40.1
unnamed: J4.19, R39.2
RIGHT: J8.R; also elsewhere on the board
ROM DISABLE: J5.42; also elsewhere on the board
VBUS: J3.1, SW2.2 (B)
VBlue: J4.7, J7.3; also elsewhere on the board
VGreen: J4.11, J7.2; also elsewhere on the board
VRed: J4.15, J7.1; also elsewhere on the board
~B7: J6.41; also elsewhere on the board
~CART: J5.35, J6.35; also elsewhere on the board
~HSync: J7.13; also elsewhere on the board
~NMI: J5.37, J6.37; also elsewhere on the board
~RESET: J5.39, J6.39; also elsewhere on the board
~R/W: J5.38, J6.38; also elsewhere on the board
~Sync: R39.1; also elsewhere on the board
~VSync: J7.14; also elsewhere on the board
~WR: J5.40, J6.40; also elsewhere on the board
